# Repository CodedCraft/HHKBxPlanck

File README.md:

# HHKBxPlanck
## A 3D Printed Ortholinear Keyboard

This repository hosts the design files and firmware for a revolutionary 3D printed keyboard, combining the ergonomic brilliance of the HHKB with the finger-friendly ortholinear layout of the Planck. Crafted entirely through 3D printing, this keyboard boasts a unique blend of form and function, integrating a Nordic nrf52840 chip and running on Zephyr RTOS with ZMK firmware.

## Features

- **Ortholinear Bliss:** Every key is strategically placed for optimal finger comfort and minimal movement.
- **HHKB-inspired Thumb Keys:** Borrowing from the HHKB's design philosophy, the thumb keys offer unparalleled accessibility.
- **Fully 3D Printed:** The entire keyboard, from the plastic plate and switch plate to the case and feet, is crafted using 3D printing technology.
- **Software Customization:** Zephyr RTOS and ZMK firmware provide a powerful platform for programming and customization.

## Hardware

- Nordic nrf52840 chip
- Fully 3D printed components: plastic plate, switch plate, case, and feet
- Cherry MX Switches and keycaps for a fully customized typing experience

## Software
### Zephyr RTOS

Leveraging the robust Zephyr RTOS allows for efficient multitasking, optimal resource utilization, and a stable foundation for firmware development.

### ZMK Firmware

The ZMK firmware provides a flexible and customizable environment for programming key mappings, macros, and other advanced features. Harness the power of ZMK to tailor your keyboard experience to perfection.

## Skills Needed

- 3D Printing Mastery: Proficiency in advanced 3D printing techniques and understanding of intricate designs.
- Embedded Systems Expertise: Familiarity with the Nordic nrf52840 chip, Zephyr RTOS, and firmware development.
- Programming Prowess: Ability to craft and modify firmware using the ZMK framework for a personalized keyboard experience.
- Electronics Enthusiast: Understanding of keyboard electronics, hand-wiring, and circuitry.

## What I Learned

This project served as a crucible for honing advanced skills in 3D modeling, electronics, and firmware development. Key takeaways include:

- Comprehensive 3D Printing: Mastered the art of designing and printing intricate components, pushing the boundaries of what's possible.
- Holistic Firmware Development: From chip-level programming with the Nordic nrf52840 to firmware customization with ZMK, this project delved deep into the heart of embedded systems.
- Innovative Problem Solving: Overcame challenges associated with 3D printing, hand-wiring, and firmware intricacies, showcasing adaptability and problem-solving skills.

Feel free to explore, contribute, and adapt this project to elevate the realms of 3D printed keyboard craftsmanship, programming, and electronics. Welcome to the future of typing!

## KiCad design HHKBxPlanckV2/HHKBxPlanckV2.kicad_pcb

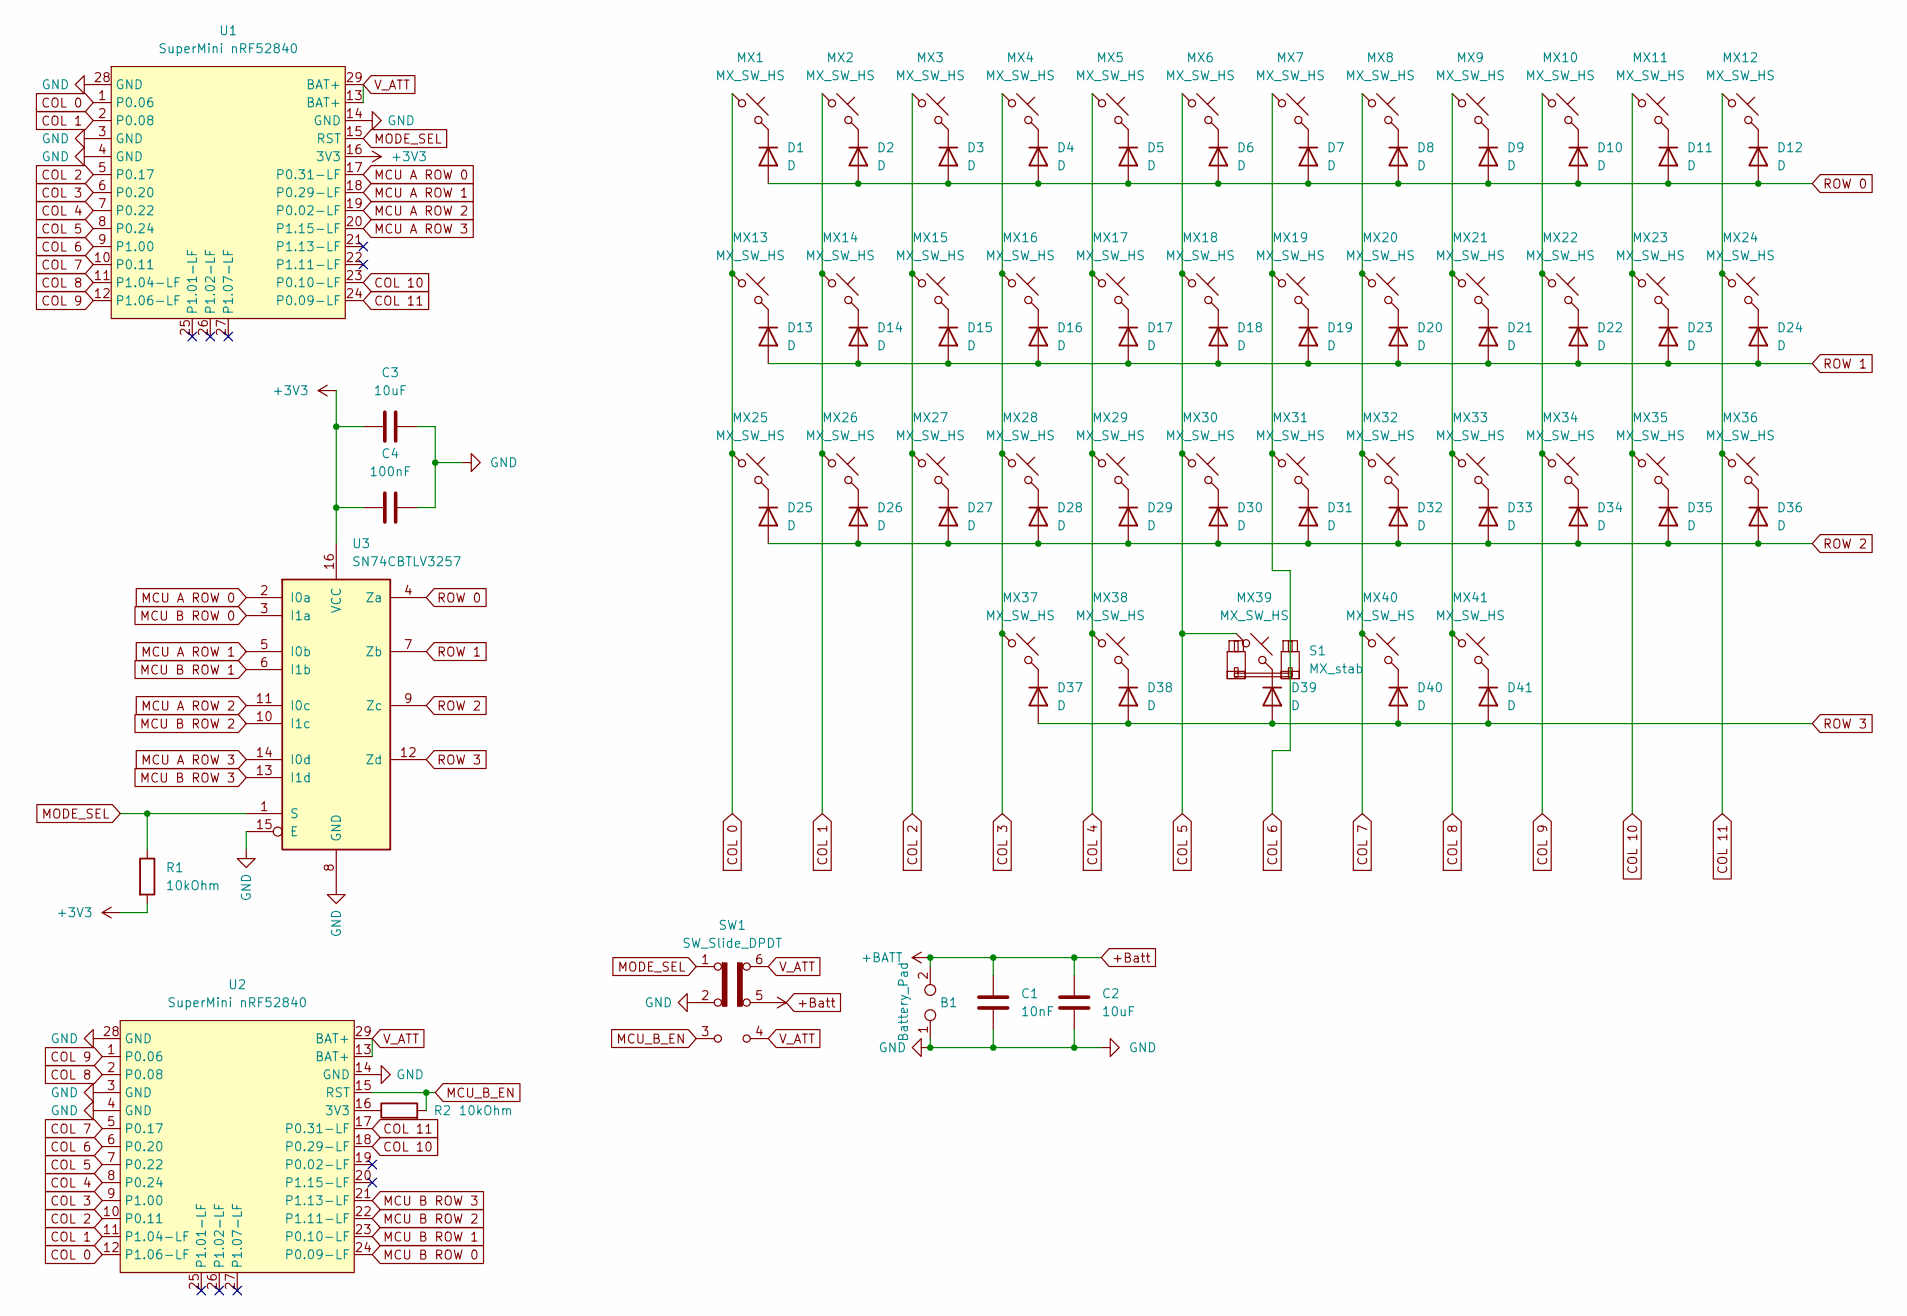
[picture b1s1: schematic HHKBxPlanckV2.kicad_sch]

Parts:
B1: Battery_Pad; TestPoint_2Pads_Pitch5.08mm_Drill1.3mm
C1: 10nF; C_0805_2012Metric; LCSC C1710
C2, C3: 10uF; C_0805_2012Metric; LCSC C15850
C4: 100nF; C_0805_2012Metric; LCSC C49678
D1, D2, D3, D4, D5, D6, D7, D8, D9, D10, D11, D12, D13, D14, D15, D16, D17, D18, D19, D20, D21, D22, D23, D24, D25, D26, D27, D28, D29, D30, D31, D32, D33, D34, D35, D36, D37, D38, D39, D40, D41: D; D_SOD-123; LCSC C81598
MX1, MX2, MX3, MX4, MX5, MX6, MX7, MX8, MX9, MX10, MX11, MX12, MX13, MX14, MX15, MX16, MX17, MX18, MX19, MX20, MX21, MX22, MX23, MX24, MX25, MX26, MX27, MX28, MX29, MX30, MX31, MX32, MX33, MX34, MX35, MX36, MX37, MX38, MX39, MX40, MX41: MX_SW_HS; SW_MX_HS_CPG151101S11_1u; LCSC C49352235
R1, R2: 10kOhm; R_0805_2012Metric; LCSC C17414
S1: MX_stab; STAB_MX_P_2u
SW1: SW_Slide_DPDT; SW_DPDT_CK_JS202011JCQN; LCSC C221664
U1, U2: SuperMini nRF52840; SuperMini_nRF52840_AH_USBup
U3: SN74CBTLV3257; TSSOP-16_4.4x5mm_P0.65mm; LCSC C7637

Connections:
+3V3: C3.1, C4.1, R1.2, U1.16 (3V3), U3.16 (VCC)
+Batt: B1.2, C1.1, C2.1, SW1.5 (B)
COL 0: MX1.1, MX13.1, MX25.1, U1.1 (P0.06), U2.12 (P1.06-LF)
COL 1: MX2.1, MX14.1, MX26.1, U1.2 (P0.08), U2.11 (P1.04-LF)
COL 2: MX3.1, MX15.1, MX27.1, U1.5 (P0.17), U2.10 (P0.11)
COL 3: MX4.1, MX16.1, MX28.1, MX37.1, U1.6 (P0.20), U2.9 (P1.00)
COL 4: MX5.1, MX17.1, MX29.1, MX38.1, U1.7 (P0.22), U2.8 (P0.24)
COL 5: MX6.1, MX18.1, MX30.1, MX39.1, U1.8 (P0.24), U2.7 (P0.22)
COL 6: MX7.1, MX19.1, MX31.1, U1.9 (P1.00), U2.6 (P0.20)
COL 7: MX8.1, MX20.1, MX32.1, MX40.1, U1.10 (P0.11), U2.5 (P0.17)
COL 8: MX9.1, MX21.1, MX33.1, MX41.1, U1.11 (P1.04-LF), U2.2 (P0.08)
COL 9: MX10.1, MX22.1, MX34.1, U1.12 (P1.06-LF), U2.1 (P0.06)
COL 10: MX11.1, MX23.1, MX35.1, U1.23 (P0.10-LF), U2.18 (P0.29-LF)
COL 11: MX12.1, MX24.1, MX36.1, U1.24 (P0.09-LF), U2.17 (P0.31-LF)
GND: B1.1, C1.2, C2.2, C3.2, C4.2, SW1.2 (B), U1.3 (GND), U1.4 (GND), U1.14 (GND), U1.28 (GND), U2.3 (GND), U2.4 (GND), U2.14 (GND), U2.28 (GND), U3.8 (GND), U3.15 (E)
MCU A ROW 0: U1.17 (P0.31-LF), U3.2 (I0a)
MCU A ROW 1: U1.18 (P0.29-LF), U3.5 (I0b)
MCU A ROW 2: U1.19 (P0.02-LF), U3.11 (I0c)
MCU A ROW 3: U1.20 (P1.15-LF), U3.14 (I0d)
MCU B ROW 0: U2.24 (P0.09-LF), U3.3 (I1a)
MCU B ROW 1: U2.23 (P0.10-LF), U3.6 (I1b)
MCU B ROW 2: U2.22 (P1.11-LF), U3.10 (I1c)
MCU B ROW 3: U2.21 (P1.13-LF), U3.13 (I1d)
MCU_B_EN: R2.2, SW1.3 (C), U2.15 (RST)
MODE_SEL: R1.1, SW1.1 (A), U1.15 (RST), U3.1 (S)
unnamed: D1.1 (K), MX1.2
unnamed: D2.1 (K), MX2.2
unnamed: D3.1 (K), MX3.2
unnamed: D4.1 (K), MX4.2
unnamed: D5.1 (K), MX5.2
unnamed: D6.1 (K), MX6.2
unnamed: D7.1 (K), MX7.2
unnamed: D8.1 (K), MX8.2
unnamed: D9.1 (K), MX9.2
unnamed: D10.1 (K), MX10.2
unnamed: D11.1 (K), MX11.2
unnamed: D12.1 (K), MX12.2
unnamed: D13.1 (K), MX13.2
unnamed: D14.1 (K), MX14.2
unnamed: D15.1 (K), MX15.2
unnamed: D16.1 (K), MX16.2
unnamed: D17.1 (K), MX17.2
unnamed: D18.1 (K), MX18.2
unnamed: D19.1 (K), MX19.2
unnamed: D20.1 (K), MX20.2
unnamed: D21.1 (K), MX21.2
unnamed: D22.1 (K), MX22.2
unnamed: D23.1 (K), MX23.2
unnamed: D24.1 (K), MX24.2
unnamed: D25.1 (K), MX25.2
unnamed: D26.1 (K), MX26.2
unnamed: D27.1 (K), MX27.2
unnamed: D28.1 (K), MX28.2
unnamed: D29.1 (K), MX29.2
unnamed: D30.1 (K), MX30.2
unnamed: D31.1 (K), MX31.2
unnamed: D32.1 (K), MX32.2
unnamed: D33.1 (K), MX33.2
unnamed: D34.1 (K), MX34.2
unnamed: D35.1 (K), MX35.2
unnamed: D36.1 (K), MX36.2
unnamed: D37.1 (K), MX37.2
unnamed: D38.1 (K), MX38.2
unnamed: D39.1 (K), MX39.2
unnamed: D40.1 (K), MX40.2
unnamed: D41.1 (K), MX41.2
unnamed: R2.1, U2.16 (3V3)
ROW 0: D1.2 (A), D2.2 (A), D3.2 (A), D4.2 (A), D5.2 (A), D6.2 (A), D7.2 (A), D8.2 (A), D9.2 (A), D10.2 (A), D11.2 (A), D12.2 (A), U3.4 (Za)
ROW 1: D13.2 (A), D14.2 (A), D15.2 (A), D16.2 (A), D17.2 (A), D18.2 (A), D19.2 (A), D20.2 (A), D21.2 (A), D22.2 (A), D23.2 (A), D24.2 (A), U3.7 (Zb)
ROW 2: D25.2 (A), D26.2 (A), D27.2 (A), D28.2 (A), D29.2 (A), D30.2 (A), D31.2 (A), D32.2 (A), D33.2 (A), D34.2 (A), D35.2 (A), D36.2 (A), U3.9 (Zc)
ROW 3: D37.2 (A), D38.2 (A), D39.2 (A), D40.2 (A), D41.2 (A), U3.12 (Zd)
V_ATT: SW1.4 (A), SW1.6 (C), U1.13 (BAT+), U1.29 (BAT+), U2.13 (BAT+), U2.29 (BAT+)

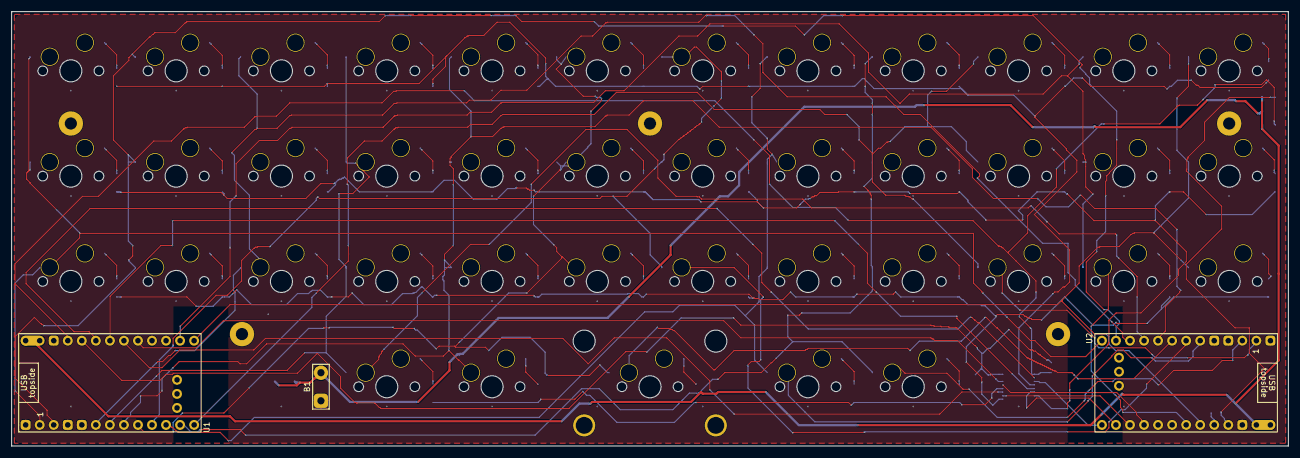
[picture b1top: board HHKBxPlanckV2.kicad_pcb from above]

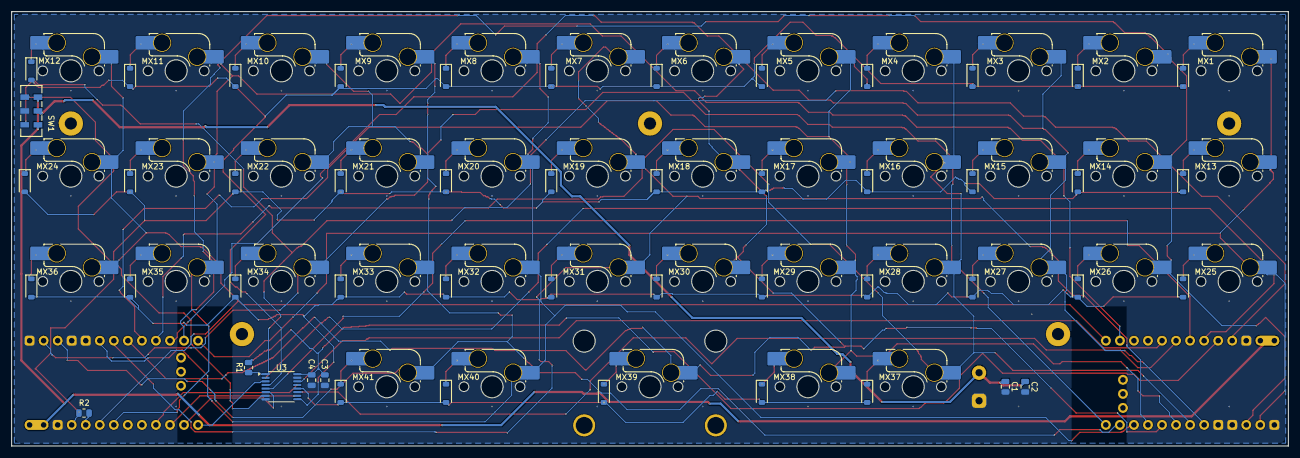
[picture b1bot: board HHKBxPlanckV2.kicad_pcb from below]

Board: 2 copper layers, 231.0 x 78.6 mm, 94 parts (90 on the bottom side), 72 nets.

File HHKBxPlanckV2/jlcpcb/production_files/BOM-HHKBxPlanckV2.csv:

Comment,Designator,Footprint,LCSC,Quantity
100nF,C4,C_0805_2012Metric,C49678,1
10kOhm,"R1,R2",R_0805_2012Metric,C17414,2
10nF,C1,C_0805_2012Metric,C1710,1
10uF,"C2,C3",C_0805_2012Metric,C15850,2
D,"D1,D10,D11,D12,D13,D14,D15,D16,D17,D18,D19,D2,D20,D21,D22,D23,D24,D25,D26,D27,D28,D29,D3,D30,D31,D32,D33,D34,D35,D36,D37,D38,D39,D4,D40,D41,D5,D6,D7,D8,D9",D_SOD-123,C81598,41
MX_SW_HS,"MX1,MX10,MX11,MX12,MX13,MX14,MX15,MX16,MX17,MX18,MX19,MX2,MX20,MX21,MX22,MX23,MX24,MX25,MX26,MX27,MX28,MX29,MX3,MX30,MX31,MX32,MX33,MX34,MX35,MX36,MX37,MX38,MX39,MX4,MX40,MX41,MX5,MX6,MX7,MX8,MX9",SW_MX_HS_CPG151101S11_1u,C49352235,41
SN74CBTLV3257,U3,TSSOP-16_4.4x5mm_P0.65mm,C7637,1
SW_Slide_DPDT,SW1,SW_DPDT_CK_JS202011JCQN,C221664,1

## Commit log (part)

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2023-12-04 Initial User Config.
2023-12-04 Project Setup
2024-01-03 Set experimental ble settings
2024-01-15 Add Readme
2024-07-16 Move F11 and F12 on Enter layer and add ALT
    F11 and F12 used to occupy LCTRL and Lower keys. They have been moved to H and N to free up the LCTRL key. RALT has been added to its original location. Reason: now ctrl and alt can be used as mods f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
2025-04-14 Update HHKBxPlanck.overlay with wakeup-source
